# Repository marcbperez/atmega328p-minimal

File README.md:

# atmega328p-minimal

Expansion board for Atmega328p.

## Installation

The schematics project is done in KiCad, free and available to most common
platforms. More information on how to download and install KiCad can be found in
its [official download page][download-kicad].

## Usage

Clone the sources and browse the package folder. The KiCad project is located in
`kicad-project/atmega328p-minimal.pro`.

```bash
git clone https://github.com/marcbperez/atmega328p-minimal
cd atmega328p-minimal
```

## Testing

There is no testing in place for this project yet.

## Troubleshooting

The [issue tracker][issue-tracker] intends to manage and compile bugs,
enhancements, proposals and tasks. Reading through its material or reporting to
its contributors via the platform is strongly recommended.

## Contributing

This project adheres to [Semantic Versioning][semver] and to certain syntax
conventions defined in [.editorconfig][editorconfig]. To get a list of changes
refer to the [CHANGELOG][changelog]. Only branches prefixed by *feature-*,
*hotfix-*, or *release-* will be considered:

  - Fork the project.
  - Create your new branch: `git checkout -b feature-my-feature develop`
  - Commit your changes: `git commit -am 'Added my new feature.'`
  - Push the branch: `git push origin feature-my-feature`
  - Submit a pull request.

## Credits

This project is created by [marcbperez][author] and maintained by its
[author][author] and contributors.

## License

This project is licensed under the [Apache License Version 2.0][license].

[author]: https://marcbperez.github.io
[issue-tracker]: https://github.com/marcbperez/atmega328p-minimal/issues
[editorconfig]: .editorconfig
[changelog]: CHANGELOG.md
[license]: LICENSE
[semver]: http://semver.org
[download-kicad]: http://kicad-pcb.org/download/

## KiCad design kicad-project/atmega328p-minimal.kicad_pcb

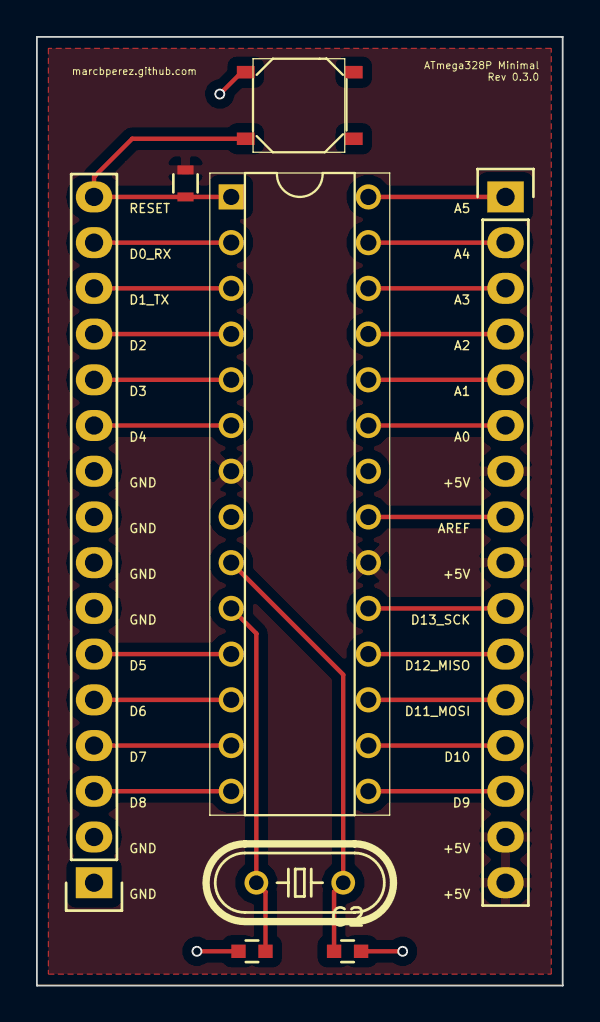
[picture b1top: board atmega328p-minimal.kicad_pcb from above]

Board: 2 copper layers, 29.2 x 52.7 mm, 8 parts (0 on the bottom side), 26 nets.

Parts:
C1, C2: 22pF; C_0603
P2, P3: CONN_01X16; Pin_Header_Straight_1x16
R1: 10k; R_0603
SW1: SMD-BUTTON_4P-5.2X5.2X1.5MM-SKQGADE010_; SW4-SMD-5.2X5.2X1.5MM
U1: MCU-ATMEGA328P-PU_DIP28_; DIP28-2.54-34.7X7.62MM
Y1: DIP-CRYSTAL-16MHZ-18PF-30PPM-40R_HC49US_; HC49US

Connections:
+5V: P3.7, P3.9, P3.15, P3.16, R1.1, U1.7, U1.20
/A0: P3.6, U1.23
/A1: P3.5, U1.24
/A2: P3.4, U1.25
/A3: P3.3, U1.26
/A4: P3.2, U1.27
/A5: P3.1, U1.28
/AREF: P3.8, U1.21
/D0_RX: P2.15, U1.2
/D1_TX: P2.14, U1.3
/D2: P2.13, U1.4
/D3: P2.12, U1.5
/D4: P2.11, U1.6
/D5: P2.6, U1.11
/D6: P2.5, U1.12
/D7: P2.4, U1.13
/D8: P2.3, U1.14
/D9: P3.14, U1.15
/D10: P3.13, U1.16
/D11_MOSI: P3.12, U1.17
/D12_MISO: P3.11, U1.18
/D13_SCK: P3.10, U1.19
/RESET: P2.16, R1.2, SW1.2, U1.1
GND: C1.2, C2.2, P2.1, P2.2, P2.7, P2.8, P2.9, P2.10, SW1.4, U1.8, U1.22
unnamed: C1.1, U1.10, Y1.1
unnamed: C2.1, U1.9, Y1.2

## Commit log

2017-09-03 Added ignore list for untracked resources.
2017-09-05 Added a .gitignore list for untracked resources.
2017-09-05 Added this CHANGELOG file to document project changes and versions.
2017-09-05 Added a README which covers project description and usage.
2017-09-05 Added a LICENSE file to define project ownership and rights.
2017-09-05 Added an EditorConfig to suggest syntax and format standards.
2017-09-06 Bumped version to 0.1.0.
2017-09-11 Added board backup file to ignore list.
2017-09-11 Added KiCad project for breakout board.
2017-09-11 Included unreleased changes.
2017-09-12 Bumped version to 0.2.0.
2017-09-15 Fixed PDF for schematics.
2017-09-15 Fixed missing sheet information and revision.
2017-09-15 Fixed PDF for board design.
2017-09-15 Bumped version to 0.2.1.
2017-09-22 Added datasheets for all components.
2017-09-23 Added gerbers for the PCB.
2017-09-25 Added Seeed OPL component libraries.
2017-09-26 Changed KiCad project, schematics and board design for this version.
2017-09-26 Added project BOM.
2017-09-27 Changed PDFs for schematics and board design.
2017-09-30 Bumped version to 0.3.0.
